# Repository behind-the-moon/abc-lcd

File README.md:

## BOOOM !!!

It worked some time, until I've decided to test shorts....
-----

I don't recommend this project, maybe, someday I make something better.

The screenshot of schematic for easier access to it

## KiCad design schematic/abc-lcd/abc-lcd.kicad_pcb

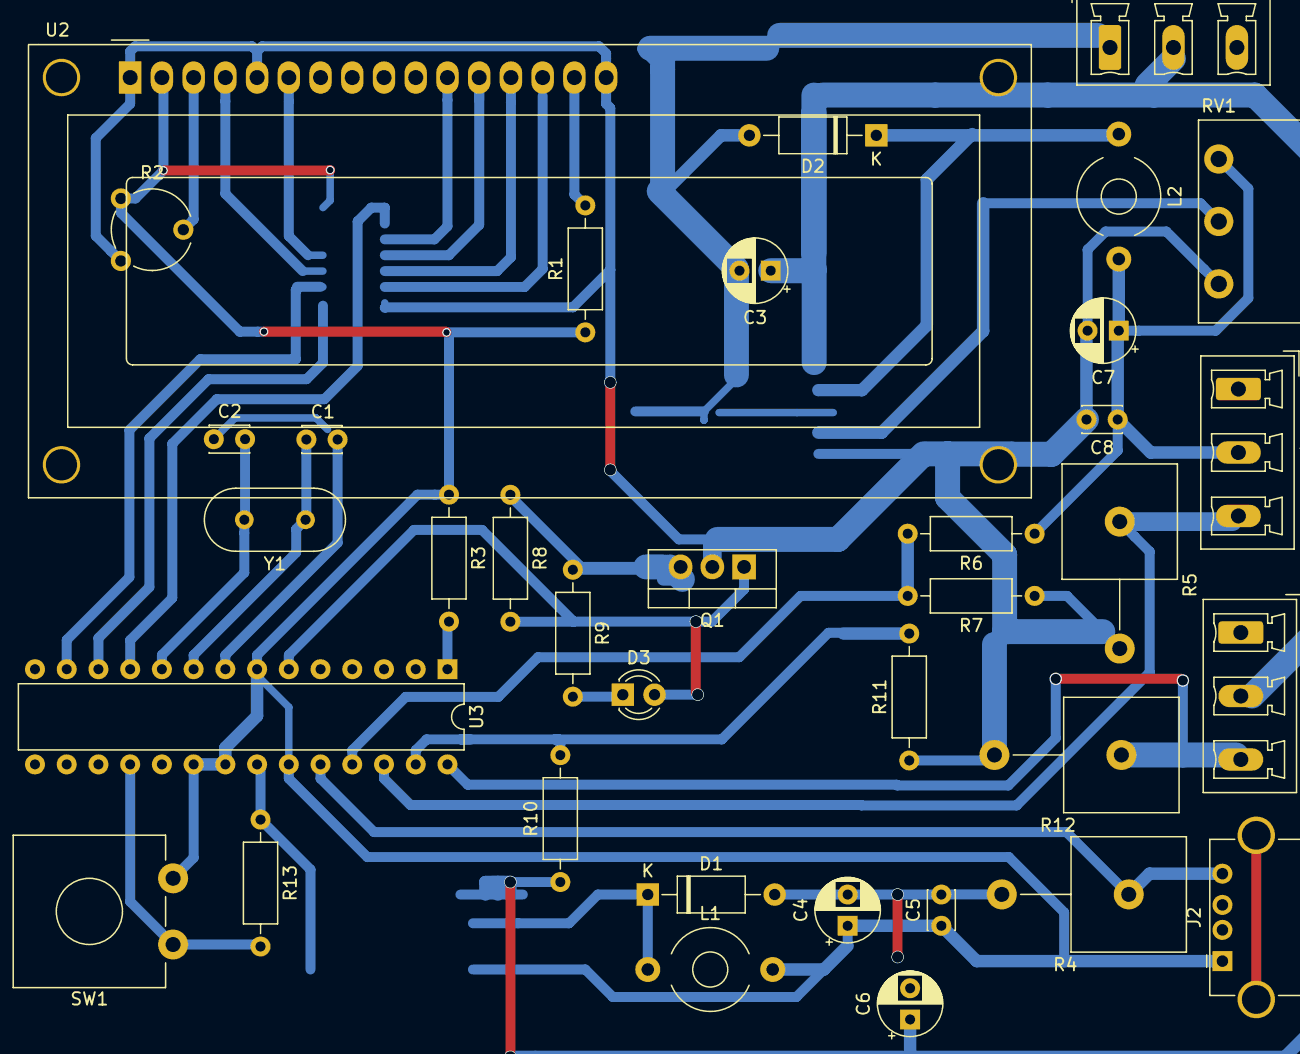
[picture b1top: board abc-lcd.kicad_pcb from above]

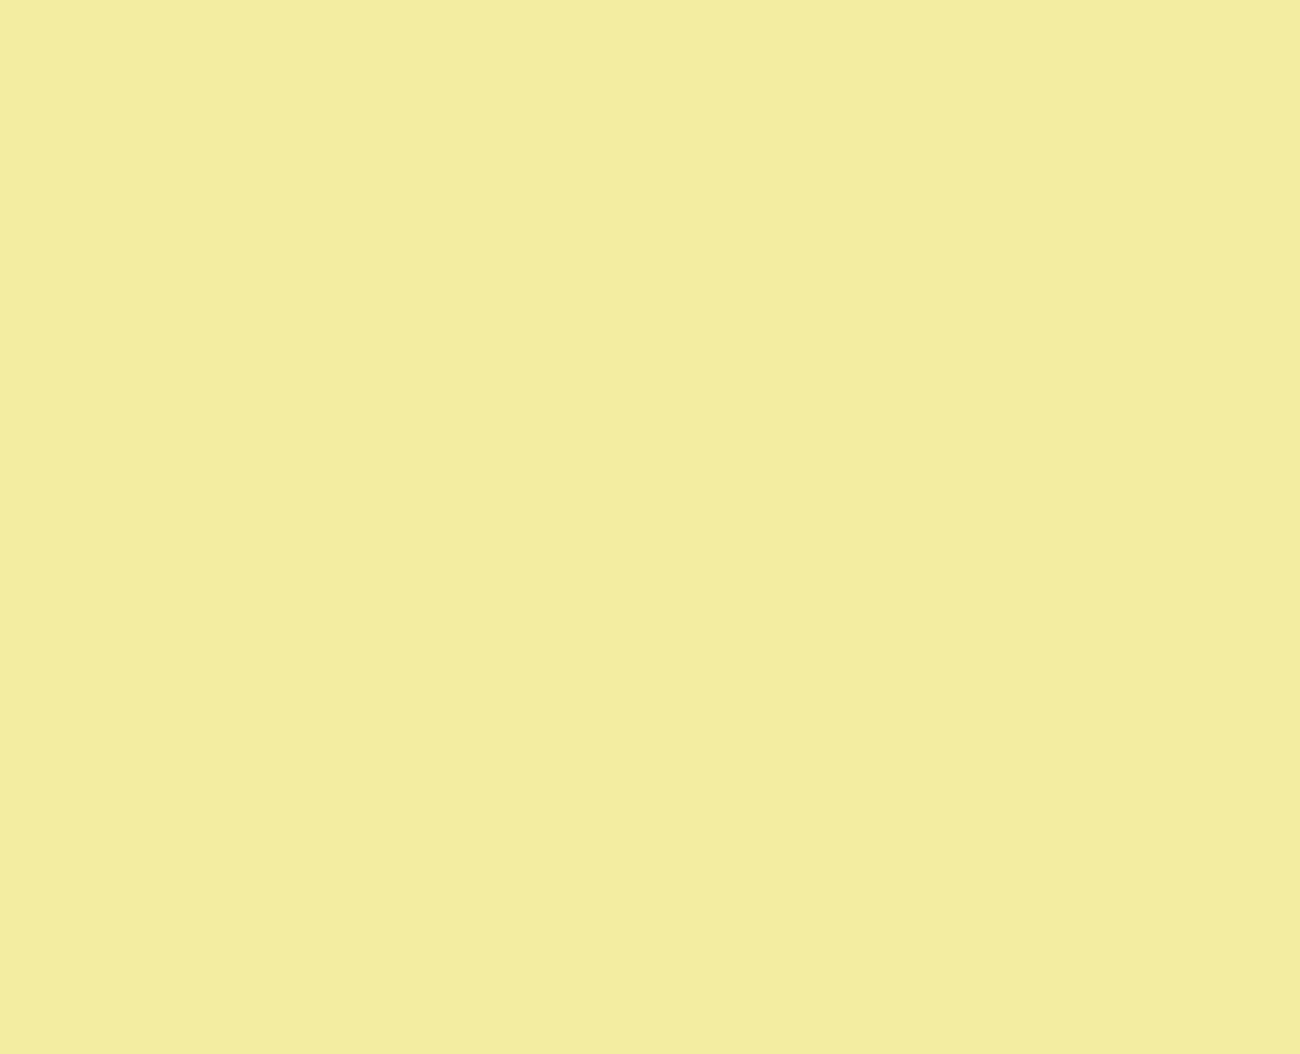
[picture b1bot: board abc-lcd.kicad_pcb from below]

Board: 2 copper layers, 39 parts (3 on the bottom side), 30 nets.

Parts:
C1, C2: 22pF; C_Disc_D3.0mm_W2.0mm_P2.50mm
C3, C6: 47uF; CP_Radial_D5.0mm_P2.50mm
C4, C7: 22uF; CP_Radial_D5.0mm_P2.50mm
C5, C8: 100nF; C_Disc_D3.0mm_W2.0mm_P2.50mm
D1, D2: D_Schottky; D_A-405_P10.16mm_Horizontal
D3: LED; LED_D3.0mm_FlatTop
J1: 24v-INPUT; PhoenixContact_MCV_1,5_3-G-5.08_1x03_P5.08mm_Vertical
J2: USB_A; USB_A_Stewart_SS-52100-001_Horizontal
J3: 24v_OUTPUT; PhoenixContact_MCV_1,5_3-G-5.08_1x03_P5.08mm_Vertical
J4: ADJ_OUTPUT; PhoenixContact_MCV_1,5_3-G-5.08_1x03_P5.08mm_Vertical
L1, L2: INDUCTOR; L_Toroid_Horizontal_D6.5mm_P10.00mm_Diameter7-5mm_Amidon-T25
Q1: IRFZ44; TO-220-3_Vertical
R1, R9: 220; R_Axial_DIN0207_L6.3mm_D2.5mm_P10.16mm_Horizontal
R2: 5K; Potentiometer_Piher_PT-6-V_Vertical
R3, R6, R8, R10, R13: 10K; R_Axial_DIN0207_L6.3mm_D2.5mm_P10.16mm_Horizontal
R4, R5, R12: 5w 10; R_Axial_Power_L25.0mm_W9.0mm_P10.16mm_Vertical
R7, R11: 1K; R_Axial_DIN0207_L6.3mm_D2.5mm_P10.16mm_Horizontal
RV1: R_POT; Potentiometer_Piher_PC-16_Single_Horizontal
SW1: SW_Push; SW_CW_GPTS203211B
U1: 74164; SOIC-14_3.9x8.7mm_P1.27mm
U2: RC1602A; WC1602A
U3: ATmega8A-PU; DIP-28_W7.62mm
U4: LM2596S-5; TO-263-5_TabPin3
U5: LM2596S-ADJ; TO-263-5_TabPin3
Y1: 16Mhz; Crystal_HC18-U_Vertical

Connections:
ADC_5S_1: J2.4, R4.1, U3.24
ADC_5V_0: C4.1, C5.1, J2.1, L1.2, R1.1, R2.3, R3.1, SW1.2, U1.14, U2.2, U3.7, U3.20, U3.21, U3.23, U4.4
ADC_24S_5: J3.3, R12.1, U3.28
ADC_24V_4: R10.2, R11.2, U3.27
ADC_ADJS_3: J4.3, R5.1, U3.26
ADC_ADJ_2: R6.2, R7.2, U3.25
BTN_SOURCE: R13.2, SW1.1, U3.18
GND: C1.1, C2.2, C3.2, C4.2, C5.2, C6.2, D1.2, D2.2, J1.1, Q1.3, R4.2, R8.1, R9.1, R13.1, U3.8, U3.22, U4.3, U4.5, U5.3
GND_ENB: C7.2, C8.2, Q1.2, R2.1, R5.2, R7.1, R11.1, R12.2, RV1.1, U1.7, U2.1, U2.5, U2.16, U5.5
LCD_CK: U1.8, U3.12
LCD_DATA: U1.1, U1.2, U3.11
LCD_RE: U1.9, U3.13
unnamed: C1.2, U3.9, Y1.1
unnamed: C2.1, U3.10, Y1.2
unnamed: C7.1, C8.1, J4.2, L2.2, R6.1, RV1.3
unnamed: D1.1, L1.1, U4.2
unnamed: D2.1, L2.1, U5.2
unnamed: D3.1, R9.2
unnamed: R1.2, U2.15
unnamed: R2.2, U2.3
unnamed: R3.2, U3.1
unnamed: RV1.2, U5.4
unnamed: U1.3, U2.11
unnamed: U1.4, U2.12
unnamed: U1.5, U2.13
unnamed: U1.6, U2.14
unnamed: U1.10, U2.4
unnamed: U1.11, U2.6
PWR_ENABLE: D3.2, Q1.1, R8.2, U3.6
v24: C3.1, C6.1, J1.2, J3.2, R10.1, U4.1, U5.1

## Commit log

2019-09-21 ADC library that works
2019-09-21 Just a voltmeter
2019-09-21 Better display resizing using smaller tails for larger values
2019-09-22 Power module schematic
2019-09-22 A bit less messy pcb but still looks like a garbage
2019-09-23 Proper component placement
2019-09-23 Complete pcb (alpha)
2019-09-23 Smaller version (not testerd yet)
2019-09-24 Schematic with 2 missing capacitors (tested)
2019-09-24 Redundant README file removed
2019-09-24 Power button support
2019-09-25 Pwr button behaviour fix
2019-09-25 BOOM!!!
2019-09-25 Illustration
2019-09-25 BOOM BOOM!!!
2019-09-25 Schematic image
2019-09-25 Board image
